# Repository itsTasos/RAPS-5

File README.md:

<p align="center">
  <strong>Redundant Avionics Power Supervisor</strong><br>
  A compact, dual-input power module for experimental UAV and robotics systems.
</p>

<p align="center">
  <a href="hardware/RAPS-5_V1.kicad_pro">KiCad project</a> ·
  <a href="docs/drawings/RAPS-5_schematic.pdf">Schematic PDF</a> ·
  <a href="manufacturing/BOM.csv">Bill of materials</a> ·
  <a href="docs/DESIGN.md">Design notes</a> ·
  <a href="validation/BENCH_VALIDATION.md">Bench validation</a>
</p>

> **Prototype status** — Schematic, PCB and fabrication exports are included. ERC, DRC and schematic-to-PCB parity checks pass under the saved project settings. **3 A continuous output is a design target; physical bench validation is pending.**

## Two paths. One purpose.

RAPS-5 brings two independently protected LiPo inputs onto a common avionics power bus. Each path has its own fuse, reverse-polarity protection, transient suppression, input filtering and buck converter. Independent ideal-diode controllers combine the regulated outputs while blocking backfeed into an inactive path.

The result is a **50 × 40 mm, four-layer PCB** with clearly labeled connectors, three voltage-status LEDs and accessible test points.

| At a glance | Design |
| :--- | :--- |
| Battery inputs | Two 2S–6S LiPo inputs; up to 25.2 V normal input |
| Local regulated outputs | Path A: 5.200 V · Path B: 5.152 V nominal |
| Continuous output | 3 A design target from either path |
| Buck converters | Two TPS54561DPRR devices, approximately 400 kHz |
| Output combining | Two LTC4412 controllers with external P-channel MOSFETs |
| PCB | 50 × 40 mm · 4 layers · 1.6 mm FR-4 · ENIG |
| Copper | 2 oz outer layers / 1 oz inner layers |
| Monitoring | PATH A OK · PATH B OK · OUTPUT OK |
| Design tool | KiCad 10; verified with 10.0.5 |

## Power architecture

```mermaid
flowchart LR
    A["BAT A<br/>2S–6S LiPo"] --> PA["5 A fuse<br/>Reverse PMOS · TVS · Filter"]
    PA --> BA["TPS54561 buck<br/>5.200 V nominal"]
    BA --> OA["LTC4412 + PMOS<br/>Ideal-diode stage"]
    B["BAT B<br/>2S–6S LiPo"] --> PB["5 A fuse<br/>Reverse PMOS · TVS · Filter"]
    PB --> BB["TPS54561 buck<br/>5.152 V nominal"]
    BB --> OB["LTC4412 + PMOS<br/>Ideal-diode stage"]
    OA --> BUS["Common 5V_BUS<br/>Bulk + ceramic capacitors"]
    OB --> BUS
    BUS --> OUT["J3<br/>Avionics output"]
    BUS -.-> MON["TPS3808<br/>Output supervision"]
    style A fill:#123e35,stroke:#58ce9e,color:#fff
    style BA fill:#123e35,stroke:#58ce9e,color:#fff
    style B fill:#15354a,stroke:#79c5f4,color:#fff
    style BB fill:#15354a,stroke:#79c5f4,color:#fff
    style BUS fill:#203b43,stroke:#96dfcf,color:#fff
```

**The positive power paths remain separate until OR-ing. Ground is shared; the inputs are not galvanically isolated.** Each path is intended to support the full load on its own. The small voltage offset nominally favors A, but does not guarantee source priority or equal current sharing.

The 5.200 V and 5.152 V figures are converter setpoints **before** the OR-ing MOSFETs. Loaded BUS voltage is lower because of MOSFET and copper losses; approximately 5.1 V at 3 A is an estimate to verify on the bench.

## Board tour

<table>
  <tr>
    <th>Top — power stages and connectors</th>
    <th>Bottom — controls and bulk capacitance</th>
  </tr>
  <tr>
    <td></td>
    <td></td>
  </tr>
</table>

*Images are CAD renders. Some components do not have 3D models; these are not photographs of an assembled or tested board.*

- **Separated channels:** Path A and Path B occupy distinct regions, with local switching power stages.
- **Power copper:** wide outer-layer routes, local pours and multiple plated barrels at main layer transitions.
- **Ground plane:** In1.Cu provides the common ground plane.
- **Mechanical fit:** four M2 clearance holes and labeled input/output polarity.
- **Bring-up access:** battery, regulated rail, BUS, GND and power-good test points.

### Connections

| Connector | Function | Pin 1 | Pin 2 |
| :--- | :--- | :--- | :--- |
| J1 | Battery A input | BAT_A positive | GND |
| J2 | Battery B input | BAT_B positive | GND |
| J3 | Avionics output | 5V_BUS positive | GND |

All three use 3.81 mm, two-pin Phoenix terminal-block footprints. PATH A OK and PATH B OK indicate converter power-good status; OUTPUT OK indicates the supervised BUS voltage. LEDs do not indicate which source is carrying current. Power-good test points have local pullups; check voltage compatibility with external logic.

## Open the design

1. Download or clone this repository and keep its directory structure intact.
2. Open [`hardware/RAPS-5_V1.kicad_pro`](hardware/RAPS-5_V1.kicad_pro) in **KiCad 10**.
3. Open the schematic editor for the four-sheet circuit, or the PCB editor for the routed board.
4. Install KiCad's standard 3D-model libraries for the available component models.

Project-local symbols and footprints are included under `hardware/libraries/`. The library tables use `${KIPRJMOD}`, so no machine-specific library paths are required. No generator or autorouter script is needed to open or edit the delivered design.

## Repository map

```text
hardware/                 Native KiCad project, four schematic sheets and PCB
  libraries/              Project-local symbols and footprints
docs/
  DESIGN.md               Circuit behavior, component choices and limits
  drawings/               Schematic, assembly and copper PDFs
  images/                 README artwork and native 3D renders
manufacturing/
  BOM.csv                 Component values, footprints and key part numbers
  placement.csv           Assembly placement export
  gerbers/                Four-layer Gerbers, drills, drill maps and job file
validation/
  erc.json                Electrical-rule check results
  drc.json                Design-rule, connectivity and parity results
  BENCH_VALIDATION.md      Physical test plan and screening criteria
  bench_results.csv       Unfilled measurement worksheet
licenses/                 Bundled KiCad library license texts
```

### Browse the deliverables

| Need | File |
| :--- | :--- |
| Review the circuit | [Four-sheet schematic](docs/drawings/RAPS-5_schematic.pdf) |
| Identify and place components | [Assembly drawing](docs/drawings/RAPS-5_assembly.pdf) · [BOM](manufacturing/BOM.csv) · [Placement](manufacturing/placement.csv) |
| Inspect the copper layers | [Copper drawing](docs/drawings/RAPS-5_copper.pdf) |
| Prepare a prototype build | [Manufacturing notes](manufacturing/README.md) · [Gerber and drill files](manufacturing/gerbers/) |
| Understand the electronics | [Detailed design notes](docs/DESIGN.md) |
| Plan the first power-up | [Bench validation procedure](validation/BENCH_VALIDATION.md) |

## Verification and next steps

| Check | Current result |
| :--- | :--- |
| ERC | 0 errors · 0 warnings |
| DRC | 0 errors · 0 warnings |
| Unconnected PCB items | 0 |
| Schematic-to-PCB parity issues | 0 |
| Thermal, ripple and load-step measurements | Pending |
| Source-disconnection and reverse-current measurements | Pending |

The JSON reports record the check date, KiCad version and ignored check categories. CAD checks establish connectivity and geometric consistency; physical tests must establish continuous-current capability, converter stability and transient behavior. See [validation notes](validation/README.md) for repeatable CLI commands.

Before an operational build, validate each path at the full load, input-voltage extremes and intended ambient temperature. Nominal input undervoltage thresholds are approximately **6.5 V startup / 6.2 V shutdown**; regulation at a deeply discharged 2S pack's 6.0 V is not promised.

This is experimental UAV/robotics hardware, without aircraft certification. The shared BUS and ground remain common failure points. There is **no independent output overvoltage disconnect**; a shorted buck high-side switch can expose the output to battery voltage.

## Project and library licensing

A license for the original board design and documentation has not yet been selected. Bundled KiCad library data retains its upstream terms and attribution; see [LICENSES.md](LICENSES.md). No open-hardware certification or license grant is implied.

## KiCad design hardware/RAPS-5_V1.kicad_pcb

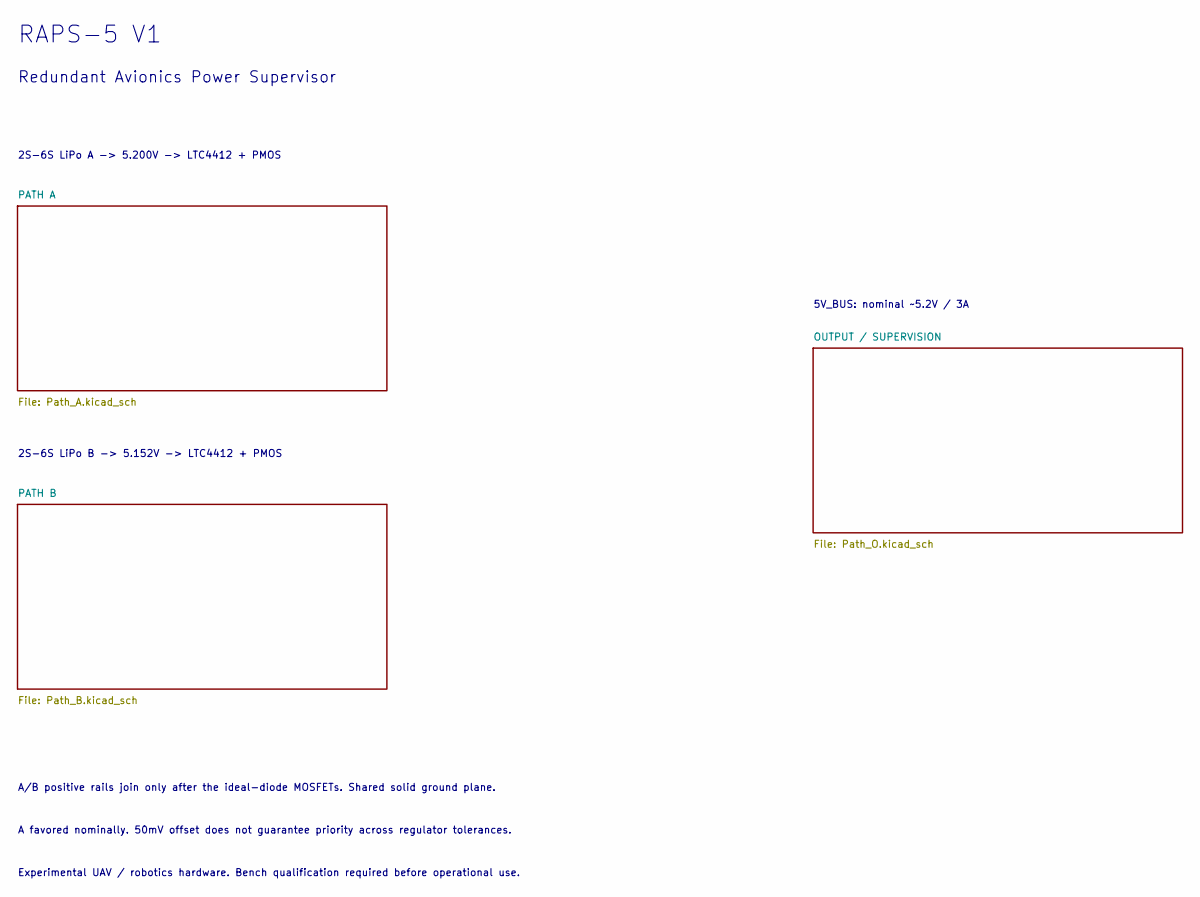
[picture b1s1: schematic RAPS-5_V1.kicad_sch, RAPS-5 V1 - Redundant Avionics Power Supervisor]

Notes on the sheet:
Experimental UAV / robotics hardware. Bench qualification required before operational use.
RAPS-5 V1
2S-6S LiPo B -> 5.152V -> LTC4412 + PMOS
Redundant Avionics Power Supervisor
5V_BUS: nominal ~5.2V / 3A
A/B positive rails join only after the ideal-diode MOSFETs. Shared solid ground plane.
A favored nominally. 50mV offset does not guarantee priority across regulator tolerances.
2S-6S LiPo A -> 5.200V -> LTC4412 + PMOS

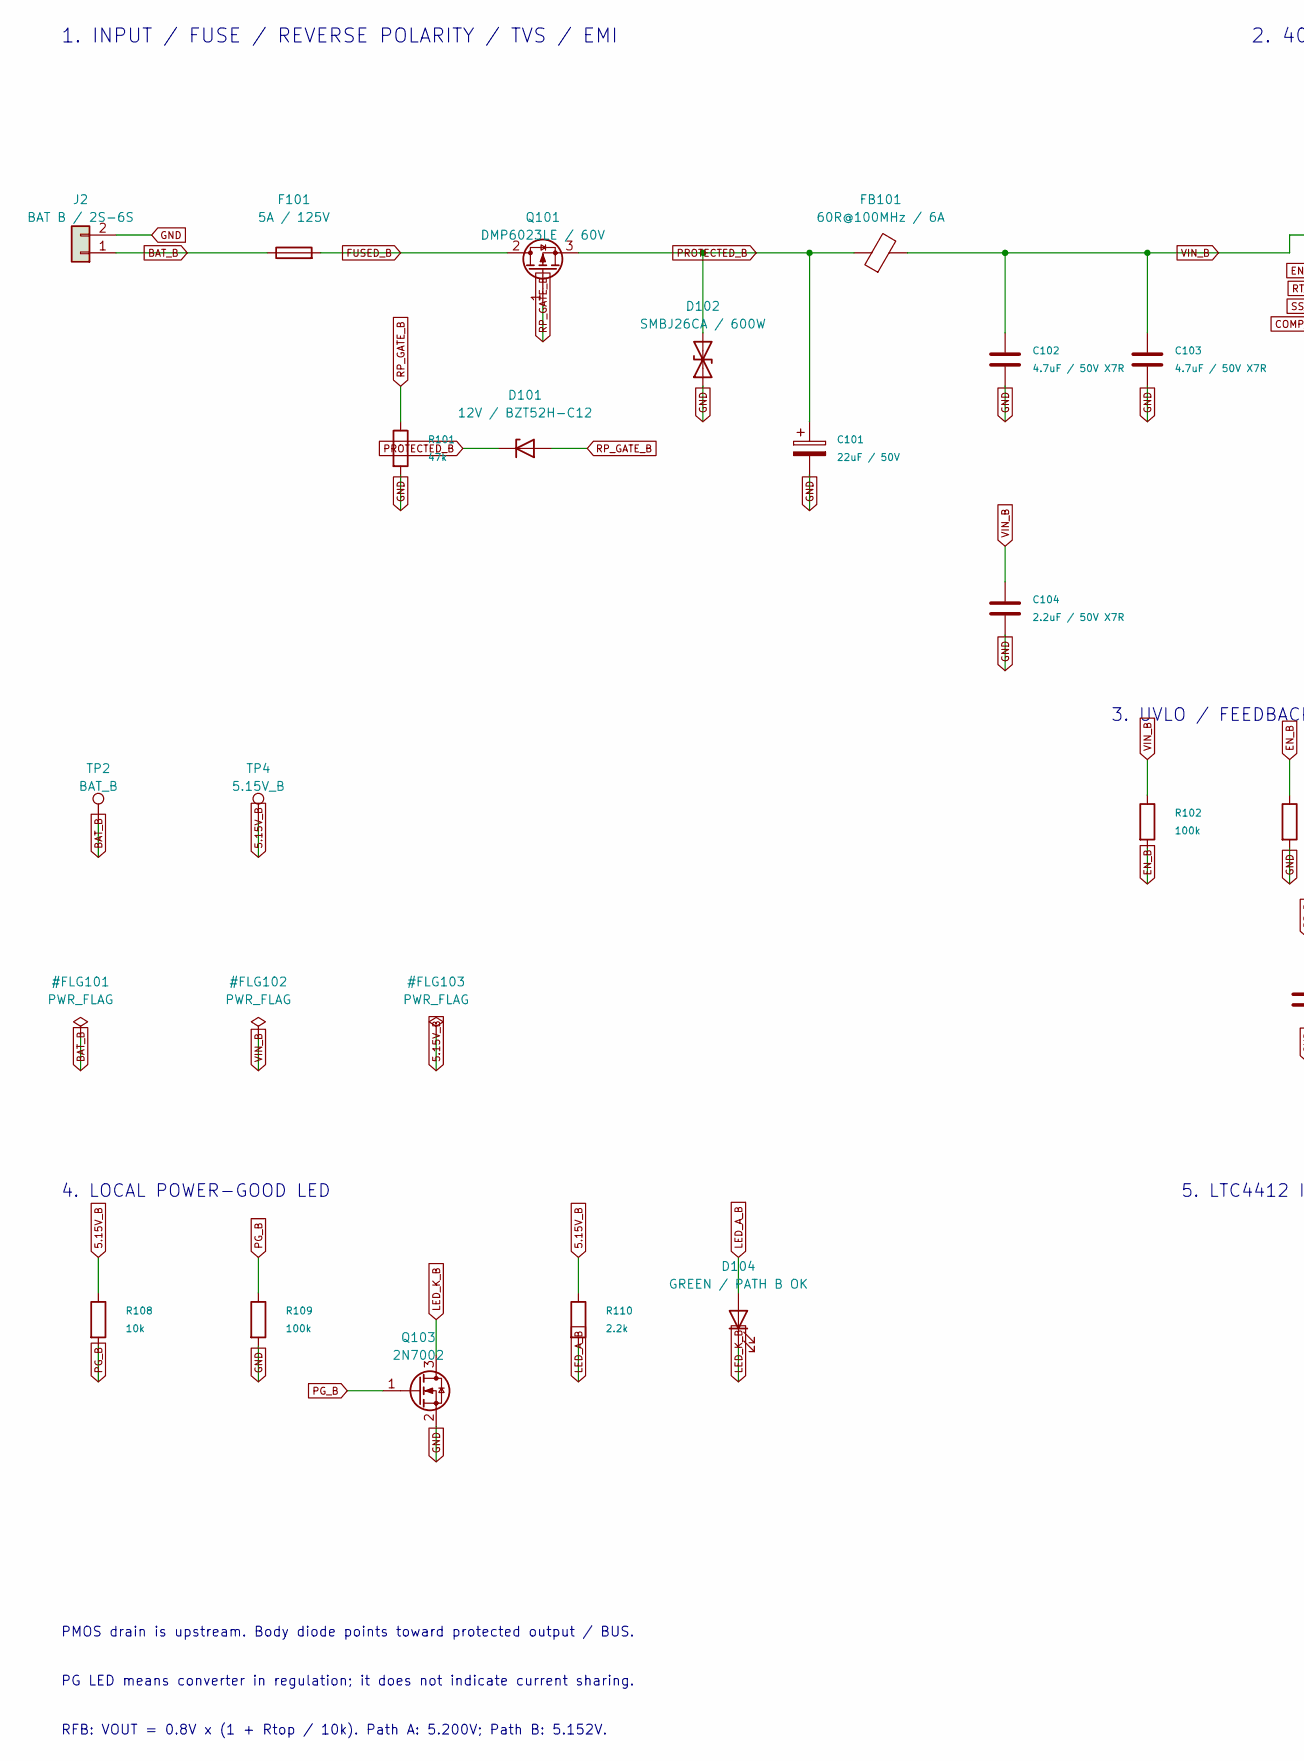
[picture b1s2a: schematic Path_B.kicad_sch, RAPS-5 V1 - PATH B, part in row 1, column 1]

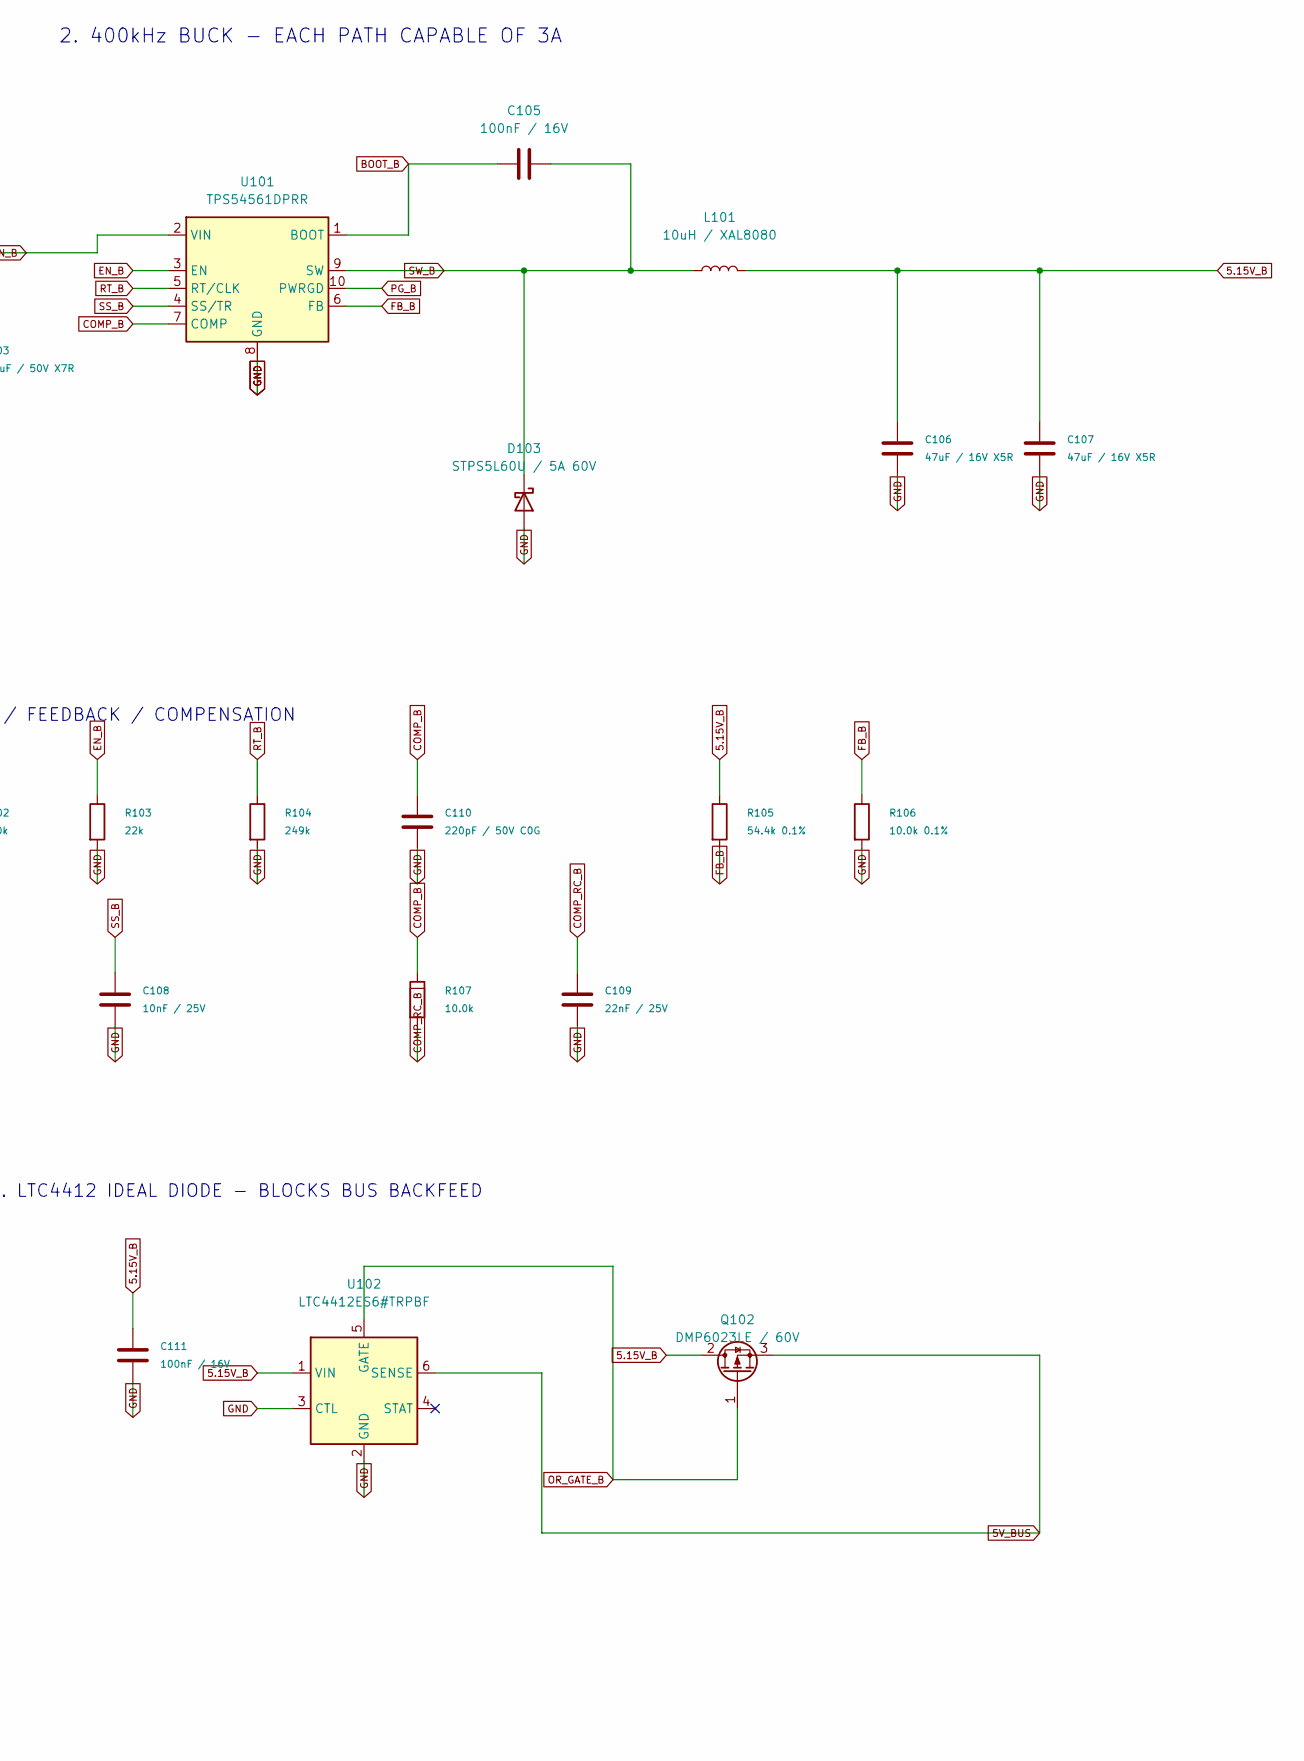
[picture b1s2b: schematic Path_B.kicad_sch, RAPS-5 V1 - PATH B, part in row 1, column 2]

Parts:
C101: 22uF / 50V; CP_Elec_6.3x7.7; MPN EEE-FK1H220P
C102, C103: 4.7uF / 50V X7R; C_1210_3225Metric; MPN GRM32ER71H475KA88L
C104: 2.2uF / 50V X7R; C_0805_2012Metric; MPN GRM21BR71H225KA12L
C105, C111: 100nF / 16V; C_0603_1608Metric; MPN GRM188R71C104KA01D
C106, C107: 47uF / 16V X5R; C_1210_3225Metric; MPN GRM32ER61C476KE15L
C108: 10nF / 25V; C_0603_1608Metric; MPN GRM188R71E103KA01D
C109: 22nF / 25V; C_0603_1608Metric; MPN GRM188R71E223KA01D
C110: 220pF / 50V C0G; C_0603_1608Metric; MPN GRM1885C1H221JA01D
D101: 12V / BZT52H-C12; D_SOD-123F; MPN BZT52H-C12
D102: SMBJ26CA / 600W; D_SMB; MPN SMBJ26CA
D103: STPS5L60U / 5A 60V; D_SMB; MPN STPS5L60U
D104: GREEN / PATH B OK; LED_0603_1608Metric; MPN LTST-C190KGKT
F101: 5A / 125V; Fuse_Littelfuse-NANO2-451_453; MPN 0451005.MRL
FB101: 60R@100MHz / 6A; L_1806_4516Metric; MPN 742792410
J2: BAT B / 2S-6S; TerminalBlock_Phoenix_MKDS-1-2-3.81_1x02_P3.81mm_Horizontal; MPN 1727010
L101: 10uH / XAL8080; L_Coilcraft_XAL8080-XXX; MPN XAL8080-103MED
Q101, Q102: DMP6023LE / 60V; SOT-223-3_TabPin2; MPN DMP6023LE-13
Q103: 2N7002; SOT-23; MPN 2N7002-7-F
R101: 47k; R_0603_1608Metric; MPN RC0603FR-0747KL
R102, R109: 100k; R_0603_1608Metric
R103: 22k; R_0603_1608Metric
R104: 249k; R_0603_1608Metric
R105: 54.4k 0.1%; R_0603_1608Metric
R106: 10.0k 0.1%; R_0603_1608Metric
R107: 10.0k; R_0603_1608Metric
R108: 10k; R_0603_1608Metric
R110: 2.2k; R_0603_1608Metric
TP2: BAT_B; TestPoint_Pad_D1.0mm
TP4: 5.15V_B; TestPoint_Pad_D1.0mm
U101: TPS54561DPRR; WSON-10-1EP_4x4mm_P0.8mm_EP2.6x3mm; MPN TPS54561DPRR
U102: LTC4412ES6#TRPBF; TSOT-23-6; MPN LTC4412ES6#TRPBF

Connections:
5.15V_B: C106.1, C107.1, C111.1, L101.2, Q102.2 (D), R105.1, R108.1, R110.1, TP4.1, U102.1 (VIN)
5V_BUS: Q102.3 (S), U102.6 (SENSE); also elsewhere on the board
BAT_B: F101.1, J2.1, TP2.1
BOOT_B: C105.1, U101.1 (BOOT)
COMP_B: C110.1, R107.1, U101.7 (COMP)
COMP_RC_B: C109.1, R107.2
EN_B: R102.2, R103.1, U101.3 (EN)
FB_B: R105.2, R106.1, U101.6 (FB)
FUSED_B: F101.2, Q101.2 (D)
GND: C101.2, C102.2, C103.2, C104.2, C106.2, C107.2, C108.2, C109.2, C110.2, C111.2, D102.1 (A1), D103.2 (A), J2.2, Q103.2 (S), R101.2, R103.2, R104.2, R106.2, R109.2, U101.8 (GND), U101.11 (GND), U102.2 (GND), U102.3 (CTL); also elsewhere on the board
LED_A_B: D104.2 (A), R110.2
LED_K_B: D104.1 (K), Q103.3 (D)
OR_GATE_B: Q102.1 (G), U102.5 (GATE)
PG_B: Q103.1 (G), R108.2, R109.1, U101.10 (PWRGD); also elsewhere on the board
PROTECTED_B: C101.1, D101.1 (K), D102.2 (A2), FB101.1, Q101.3 (S)
RP_GATE_B: D101.2 (A), Q101.1 (G), R101.1
RT_B: R104.1, U101.5 (RT/CLK)
SS_B: C108.1, U101.4 (SS/TR)
SW_B: C105.2, D103.1 (K), L101.1, U101.9 (SW)
VIN_B: C102.1, C103.1, C104.1, FB101.2, R102.1, U101.2 (VIN)

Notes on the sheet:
1. INPUT / FUSE / REVERSE POLARITY / TVS / EMI
4. LOCAL POWER-GOOD LED
5. LTC4412 IDEAL DIODE - BLOCKS BUS BACKFEED
2. 400kHz BUCK - EACH PATH CAPABLE OF 3A
PG LED means converter in regulation; it does not indicate current sharing.
RFB: VOUT = 0.8V x (1 + Rtop / 10k). Path A: 5.200V; Path B: 5.152V.
PMOS drain is upstream. Body diode points toward protected output / BUS.
3. UVLO / FEEDBACK / COMPENSATION

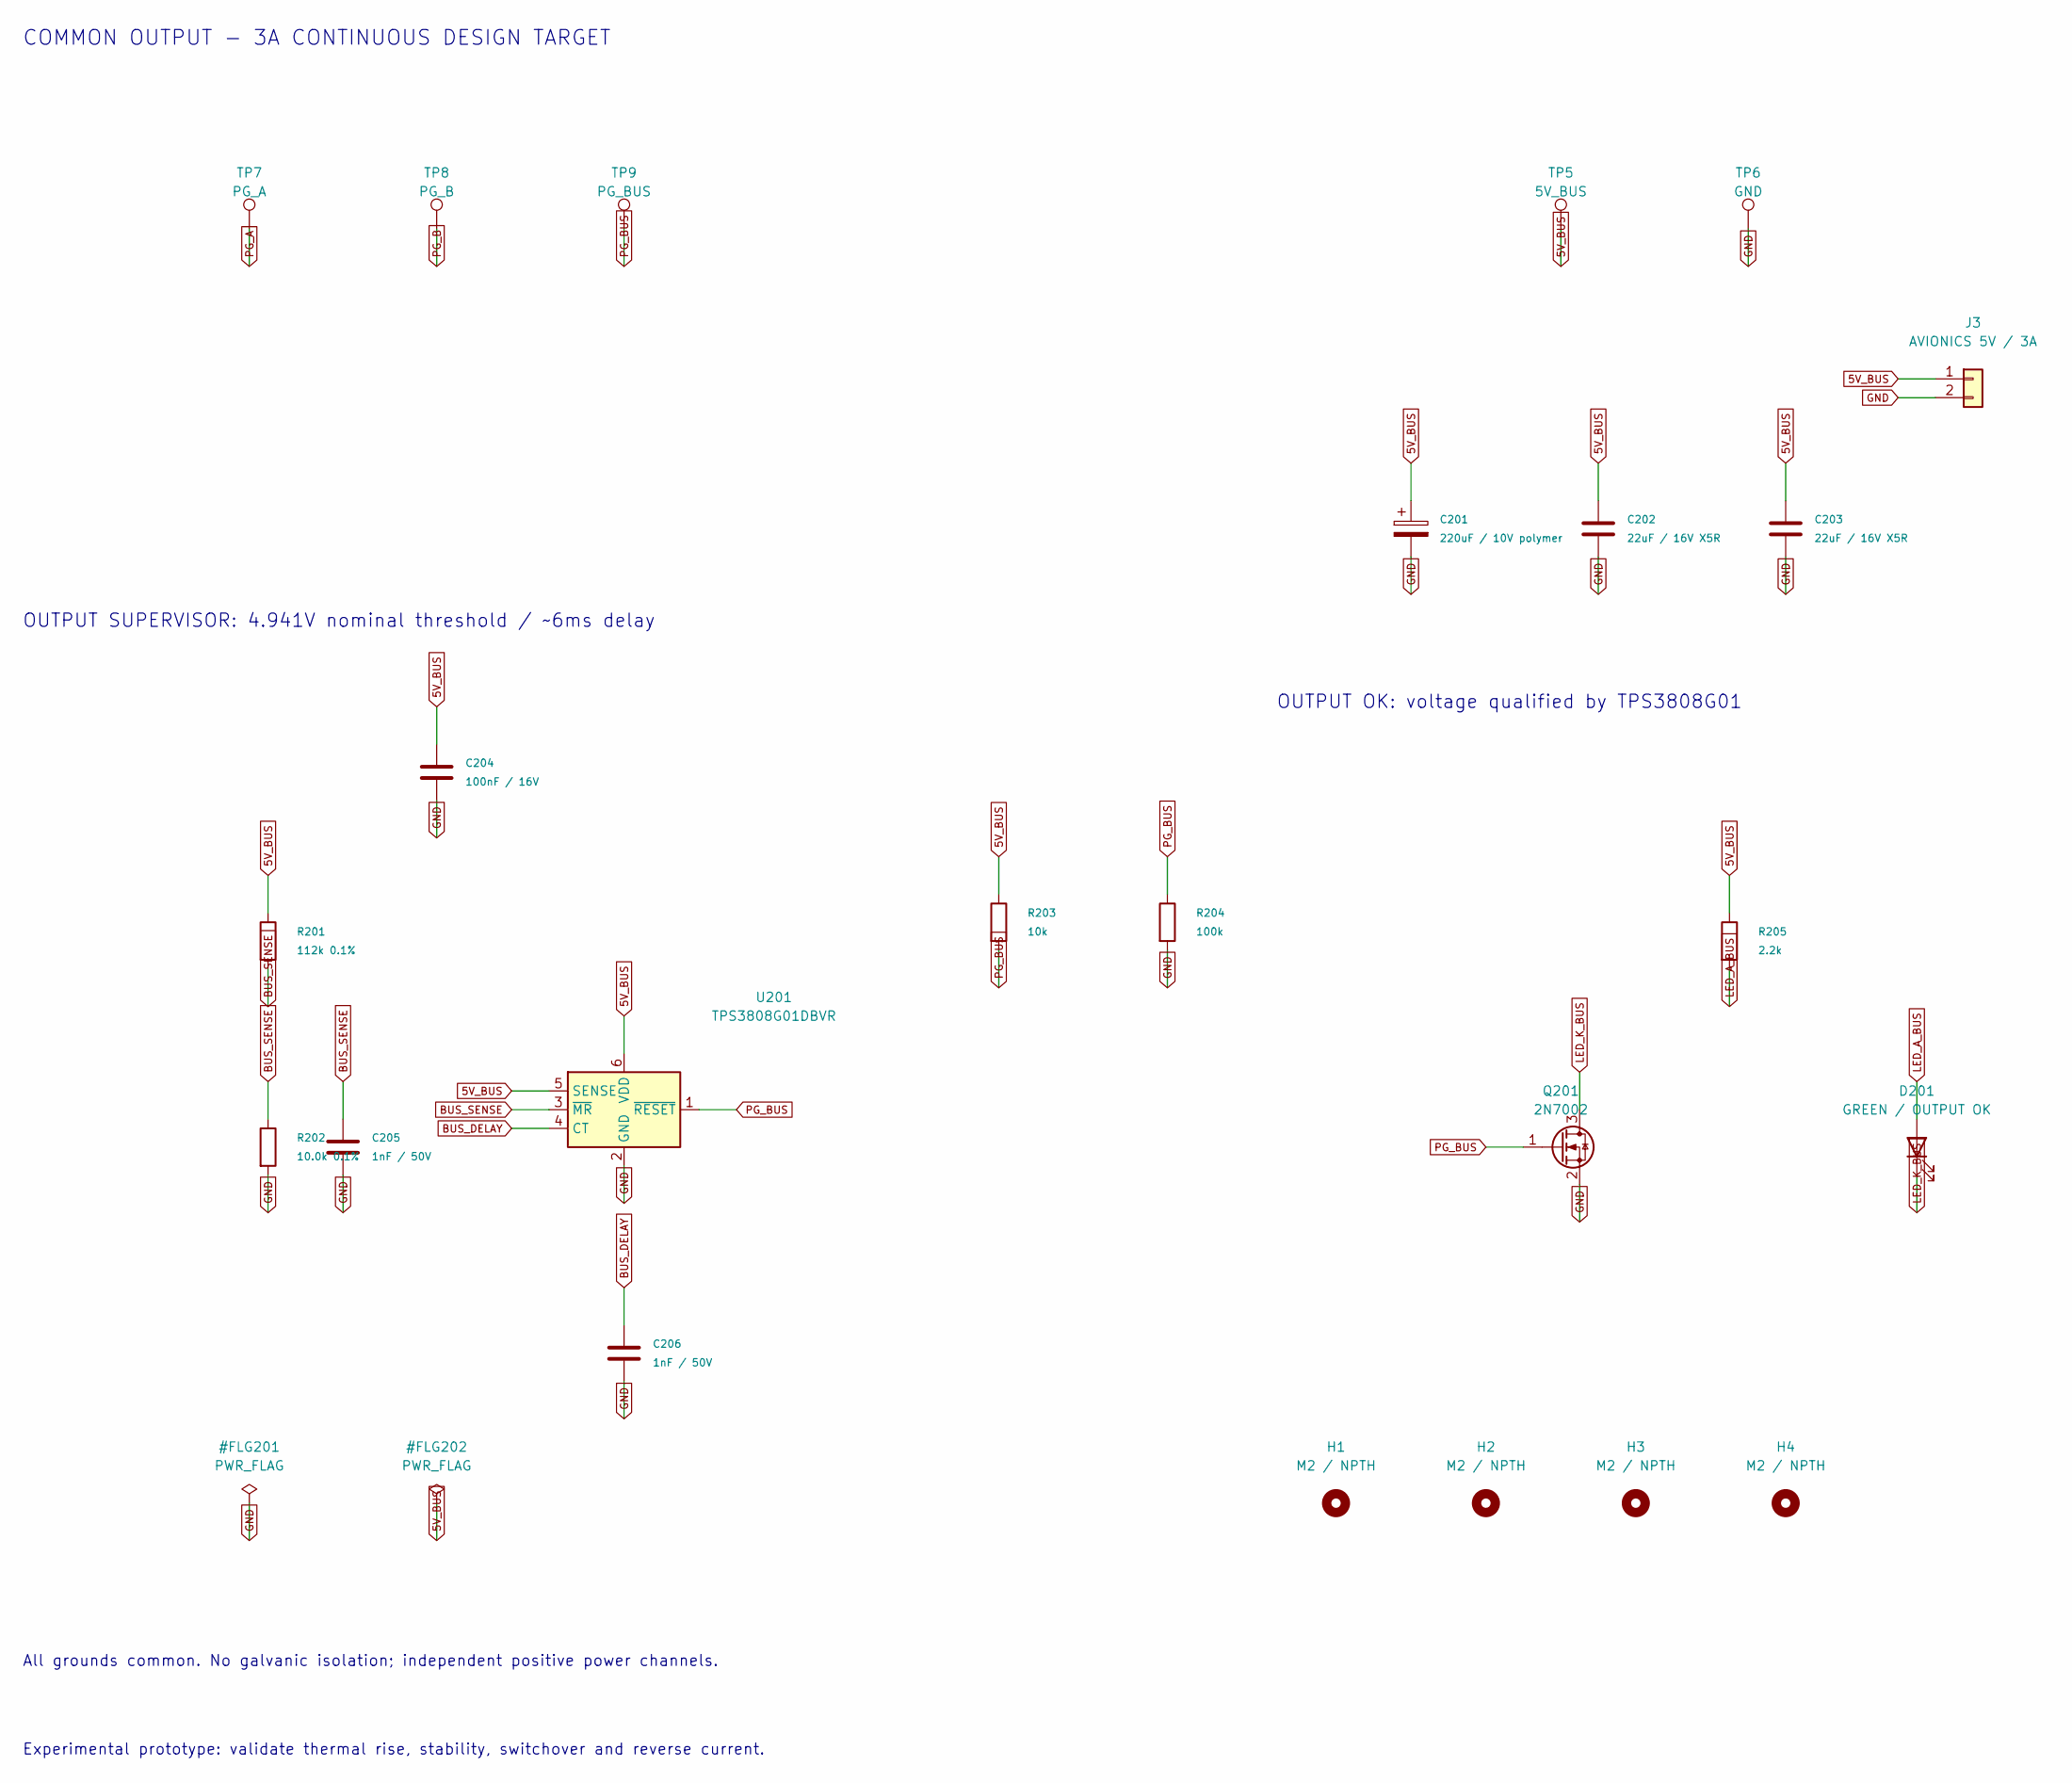
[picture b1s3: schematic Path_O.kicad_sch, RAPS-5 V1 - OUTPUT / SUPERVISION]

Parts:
C201: 220uF / 10V polymer; CP_Elec_8x6.7; MPN 10SVPF220M
C202, C203: 22uF / 16V X5R; C_1206_3216Metric; MPN GRM31CR61C226KE15L
C204: 100nF / 16V; C_0603_1608Metric
C205, C206: 1nF / 50V; C_0603_1608Metric
D201: GREEN / OUTPUT OK; LED_0603_1608Metric; MPN LTST-C190KGKT
H1, H2, H3, H4: M2 / NPTH; MountingHole_2.2mm_M2
J3: AVIONICS 5V / 3A; TerminalBlock_Phoenix_MKDS-1-2-3.81_1x02_P3.81mm_Horizontal; MPN 1727010
Q201: 2N7002; SOT-23; MPN 2N7002-7-F
R201: 112k 0.1%; R_0603_1608Metric
R202: 10.0k 0.1%; R_0603_1608Metric
R203: 10k; R_0603_1608Metric
R204: 100k; R_0603_1608Metric
R205: 2.2k; R_0603_1608Metric
TP5: 5V_BUS; TestPoint_Pad_D1.0mm
TP6: GND; TestPoint_Pad_D1.0mm
TP7: PG_A; TestPoint_Pad_D1.0mm
TP8: PG_B; TestPoint_Pad_D1.0mm
TP9: PG_BUS; TestPoint_Pad_D1.0mm
U201: TPS3808G01DBVR; SOT-23-6; MPN TPS3808G01DBVR

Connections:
5V_BUS: C201.1, C202.1, C203.1, C204.1, J3.1, R201.1, R203.1, R205.1, TP5.1, U201.5 (SENSE), U201.6 (VDD); also elsewhere on the board
BUS_DELAY: C206.1, U201.4 (CT)
BUS_SENSE: C205.1, R201.2, R202.1, U201.3 (~MR)
GND: C201.2, C202.2, C203.2, C204.2, C205.2, C206.2, J3.2, Q201.2 (S), R202.2, R204.2, TP6.1, U201.2 (GND); also elsewhere on the board
LED_A_BUS: D201.2 (A), R205.2
LED_K_BUS: D201.1 (K), Q201.3 (D)
PG_A: TP7.1; also elsewhere on the board
PG_B: TP8.1; also elsewhere on the board
PG_BUS: Q201.1 (G), R203.2, R204.1, TP9.1, U201.1 (~RESET)

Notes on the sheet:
Experimental prototype: validate thermal rise, stability, switchover and reverse current.
All grounds common. No galvanic isolation; independent positive power channels.
COMMON OUTPUT - 3A CONTINUOUS DESIGN TARGET
OUTPUT OK: voltage qualified by TPS3808G01
OUTPUT SUPERVISOR: 4.941V nominal threshold / ~6ms delay

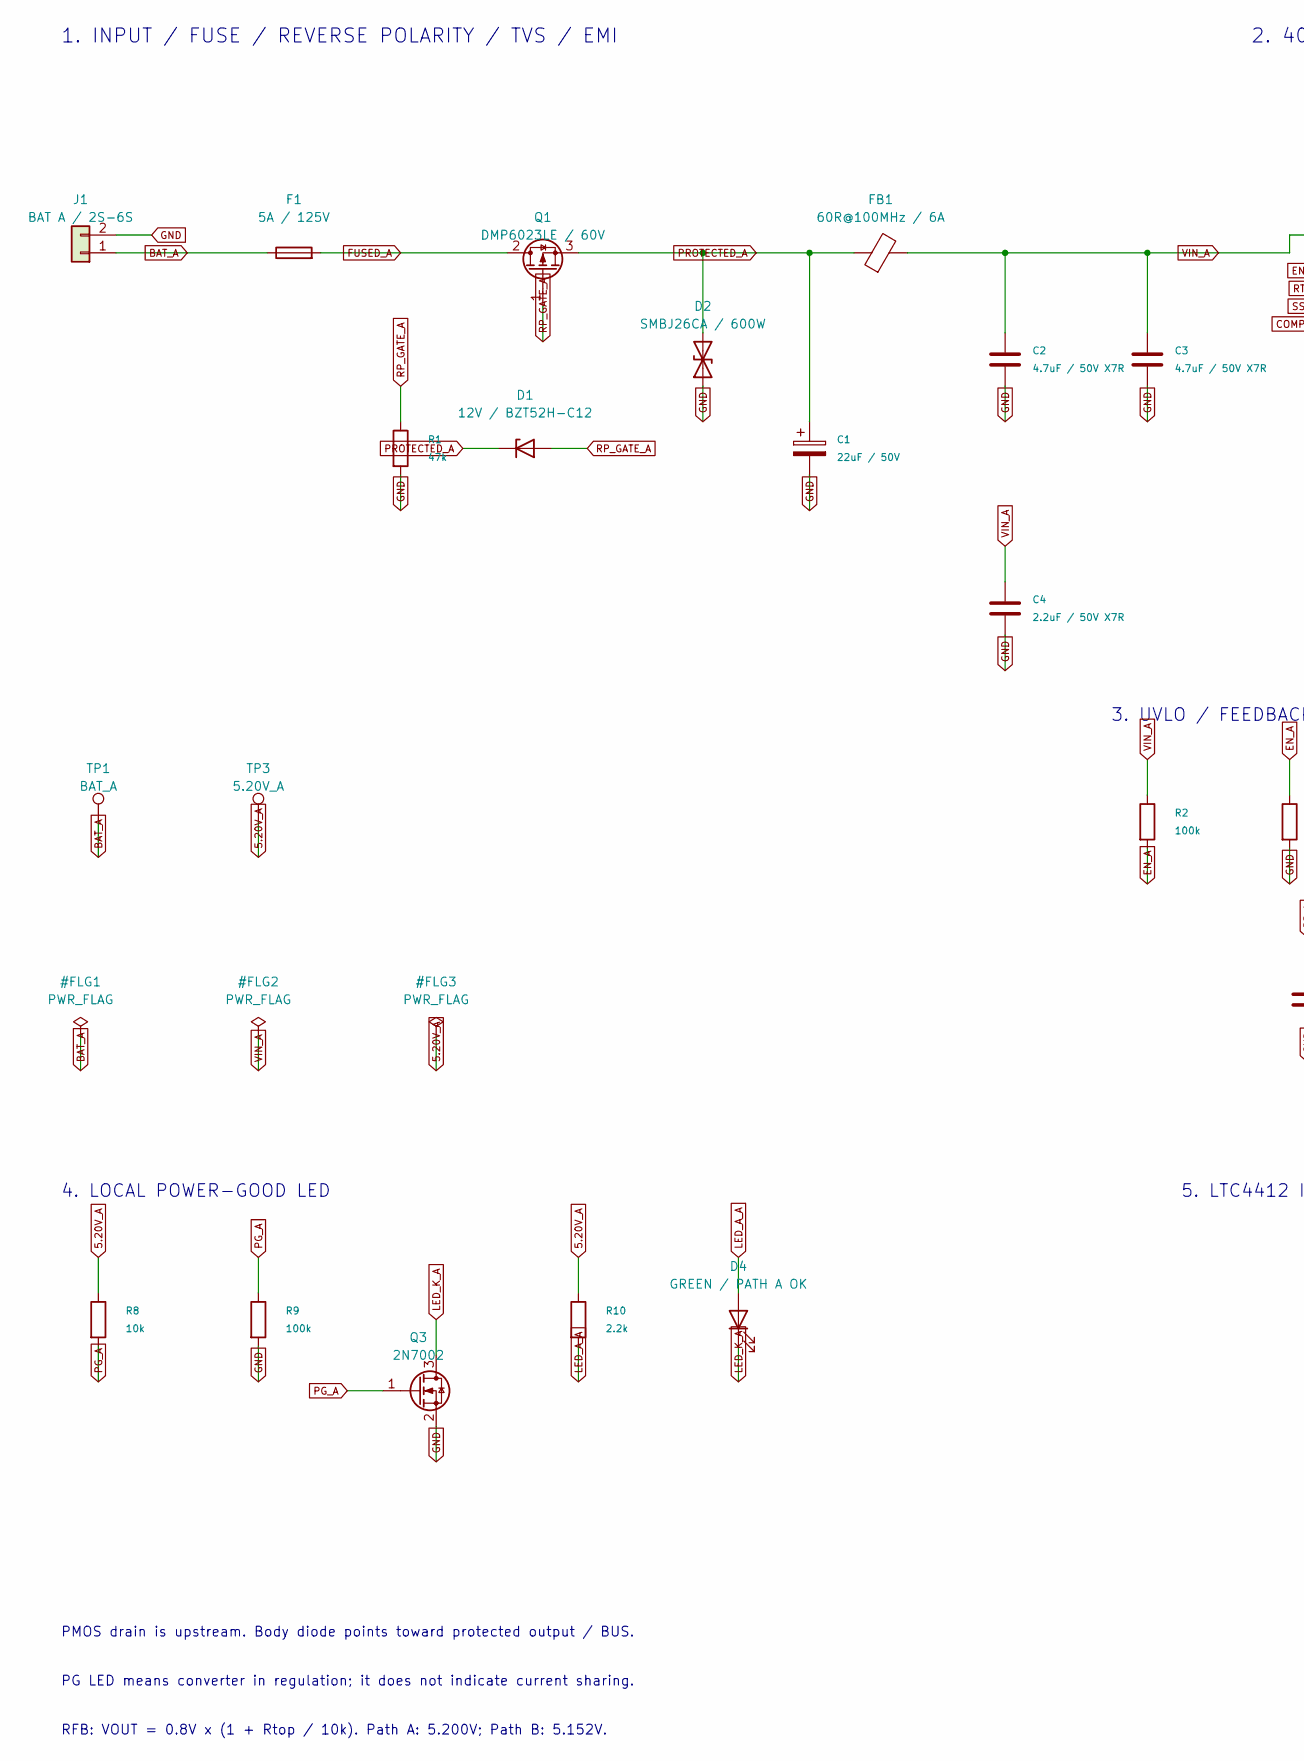
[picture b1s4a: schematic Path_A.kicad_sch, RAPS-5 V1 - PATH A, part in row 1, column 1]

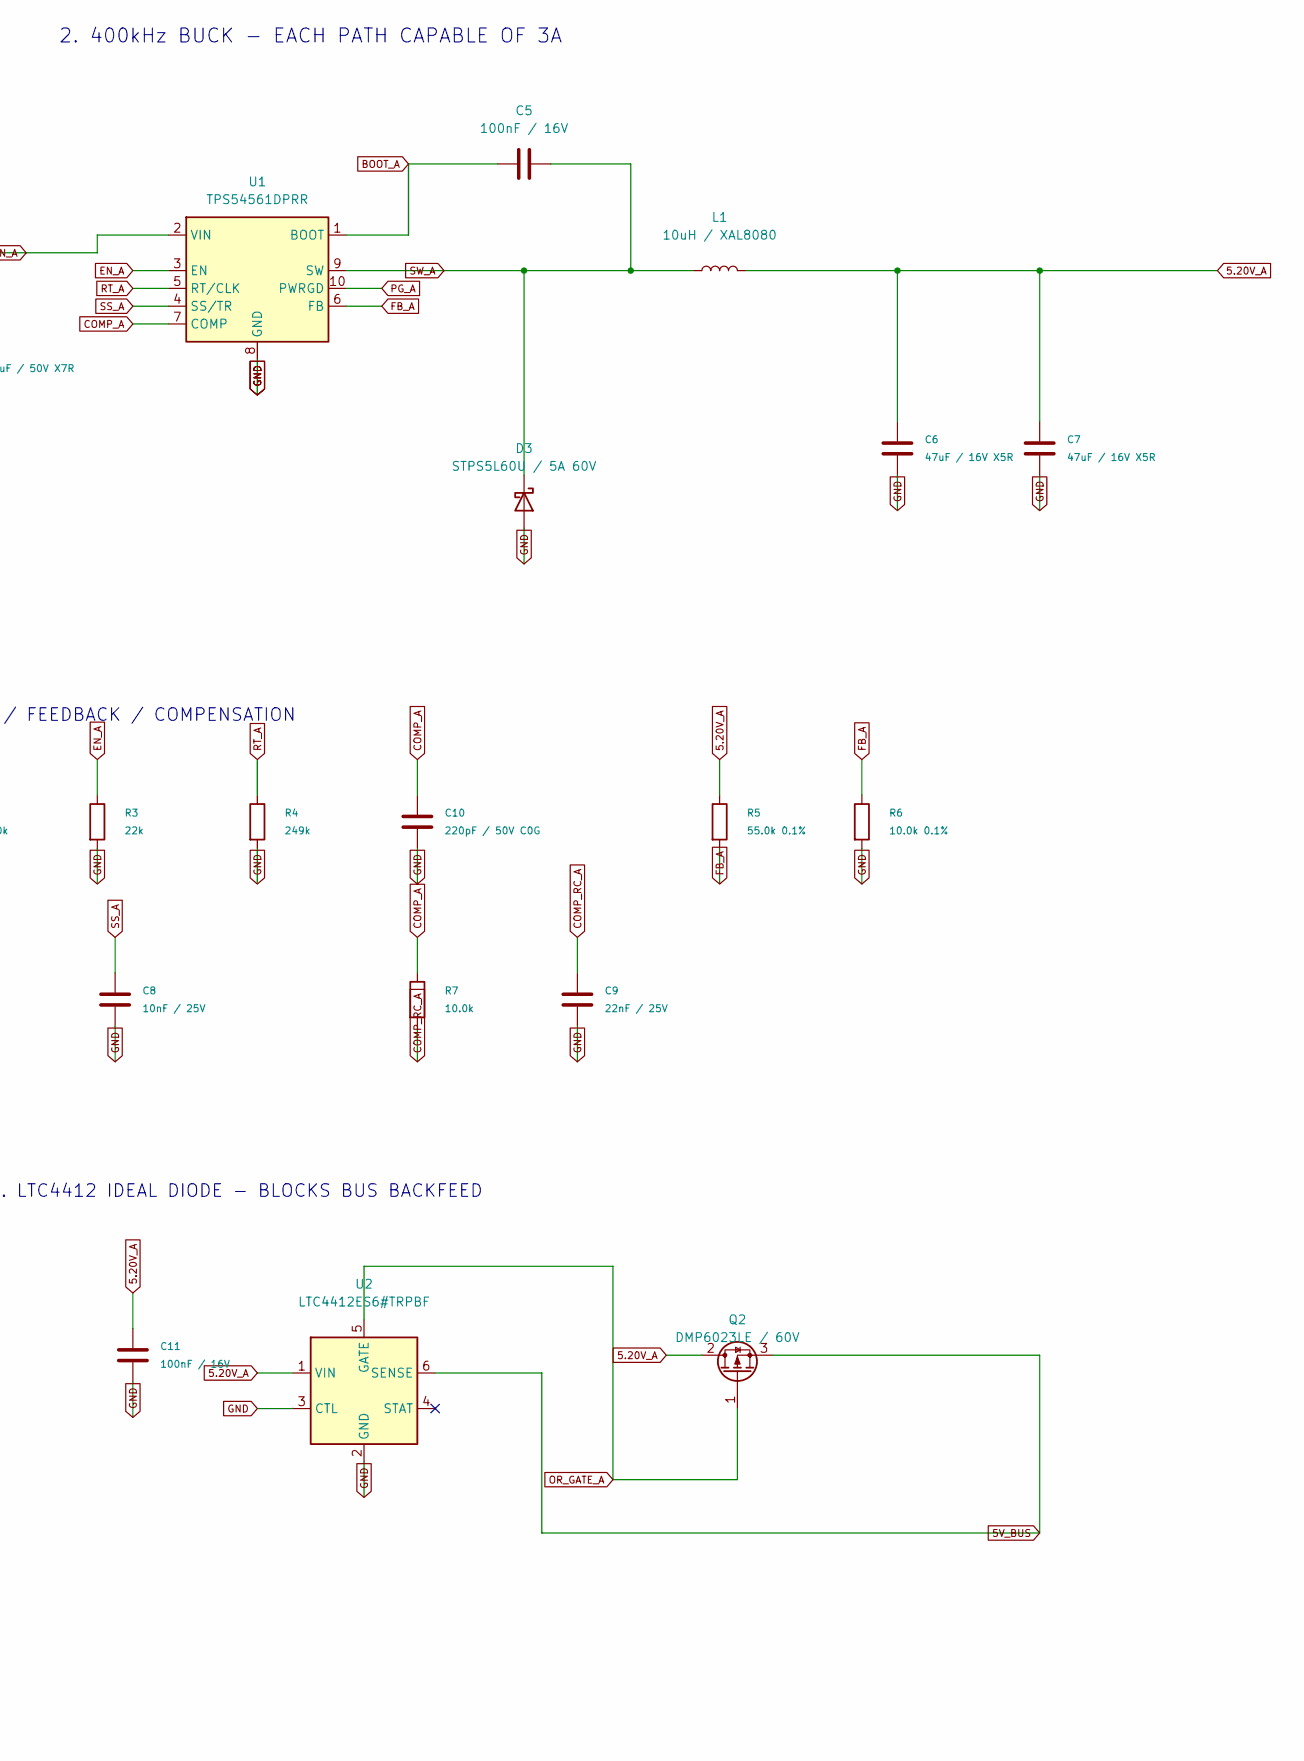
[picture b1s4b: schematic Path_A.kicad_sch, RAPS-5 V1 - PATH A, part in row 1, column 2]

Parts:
C1: 22uF / 50V; CP_Elec_6.3x7.7; MPN EEE-FK1H220P
C2, C3: 4.7uF / 50V X7R; C_1210_3225Metric; MPN GRM32ER71H475KA88L
C4: 2.2uF / 50V X7R; C_0805_2012Metric; MPN GRM21BR71H225KA12L
C5, C11: 100nF / 16V; C_0603_1608Metric; MPN GRM188R71C104KA01D
C6, C7: 47uF / 16V X5R; C_1210_3225Metric; MPN GRM32ER61C476KE15L
C8: 10nF / 25V; C_0603_1608Metric; MPN GRM188R71E103KA01D
C9: 22nF / 25V; C_0603_1608Metric; MPN GRM188R71E223KA01D
C10: 220pF / 50V C0G; C_0603_1608Metric; MPN GRM1885C1H221JA01D
D1: 12V / BZT52H-C12; D_SOD-123F; MPN BZT52H-C12
D2: SMBJ26CA / 600W; D_SMB; MPN SMBJ26CA
D3: STPS5L60U / 5A 60V; D_SMB; MPN STPS5L60U
D4: GREEN / PATH A OK; LED_0603_1608Metric; MPN LTST-C190KGKT
F1: 5A / 125V; Fuse_Littelfuse-NANO2-451_453; MPN 0451005.MRL
FB1: 60R@100MHz / 6A; L_1806_4516Metric; MPN 742792410
J1: BAT A / 2S-6S; TerminalBlock_Phoenix_MKDS-1-2-3.81_1x02_P3.81mm_Horizontal; MPN 1727010
L1: 10uH / XAL8080; L_Coilcraft_XAL8080-XXX; MPN XAL8080-103MED
Q1, Q2: DMP6023LE / 60V; SOT-223-3_TabPin2; MPN DMP6023LE-13
Q3: 2N7002; SOT-23; MPN 2N7002-7-F
R1: 47k; R_0603_1608Metric; MPN RC0603FR-0747KL
R2, R9: 100k; R_0603_1608Metric
R3: 22k; R_0603_1608Metric
R4: 249k; R_0603_1608Metric
R5: 55.0k 0.1%; R_0603_1608Metric
R6: 10.0k 0.1%; R_0603_1608Metric
R7: 10.0k; R_0603_1608Metric
R8: 10k; R_0603_1608Metric
R10: 2.2k; R_0603_1608Metric
TP1: BAT_A; TestPoint_Pad_D1.0mm
TP3: 5.20V_A; TestPoint_Pad_D1.0mm
U1: TPS54561DPRR; WSON-10-1EP_4x4mm_P0.8mm_EP2.6x3mm; MPN TPS54561DPRR
U2: LTC4412ES6#TRPBF; TSOT-23-6; MPN LTC4412ES6#TRPBF

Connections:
5.20V_A: C6.1, C7.1, C11.1, L1.2, Q2.2 (D), R5.1, R8.1, R10.1, TP3.1, U2.1 (VIN)
5V_BUS: Q2.3 (S), U2.6 (SENSE); also elsewhere on the board
BAT_A: F1.1, J1.1, TP1.1
BOOT_A: C5.1, U1.1 (BOOT)
COMP_A: C10.1, R7.1, U1.7 (COMP)
COMP_RC_A: C9.1, R7.2
EN_A: R2.2, R3.1, U1.3 (EN)
FB_A: R5.2, R6.1, U1.6 (FB)
FUSED_A: F1.2, Q1.2 (D)
GND: C1.2, C2.2, C3.2, C4.2, C6.2, C7.2, C8.2, C9.2, C10.2, C11.2, D2.1 (A1), D3.2 (A), J1.2, Q3.2 (S), R1.2, R3.2, R4.2, R6.2, R9.2, U1.8 (GND), U1.11 (GND), U2.2 (GND), U2.3 (CTL); also elsewhere on the board
LED_A_A: D4.2 (A), R10.2
LED_K_A: D4.1 (K), Q3.3 (D)
OR_GATE_A: Q2.1 (G), U2.5 (GATE)
PG_A: Q3.1 (G), R8.2, R9.1, U1.10 (PWRGD); also elsewhere on the board
PROTECTED_A: C1.1, D1.1 (K), D2.2 (A2), FB1.1, Q1.3 (S)
RP_GATE_A: D1.2 (A), Q1.1 (G), R1.1
RT_A: R4.1, U1.5 (RT/CLK)
SS_A: C8.1, U1.4 (SS/TR)
SW_A: C5.2, D3.1 (K), L1.1, U1.9 (SW)
VIN_A: C2.1, C3.1, C4.1, FB1.2, R2.1, U1.2 (VIN)

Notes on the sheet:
1. INPUT / FUSE / REVERSE POLARITY / TVS / EMI
4. LOCAL POWER-GOOD LED
5. LTC4412 IDEAL DIODE - BLOCKS BUS BACKFEED
2. 400kHz BUCK - EACH PATH CAPABLE OF 3A
PG LED means converter in regulation; it does not indicate current sharing.
RFB: VOUT = 0.8V x (1 + Rtop / 10k). Path A: 5.200V; Path B: 5.152V.
PMOS drain is upstream. Body diode points toward protected output / BUS.
3. UVLO / FEEDBACK / COMPENSATION
